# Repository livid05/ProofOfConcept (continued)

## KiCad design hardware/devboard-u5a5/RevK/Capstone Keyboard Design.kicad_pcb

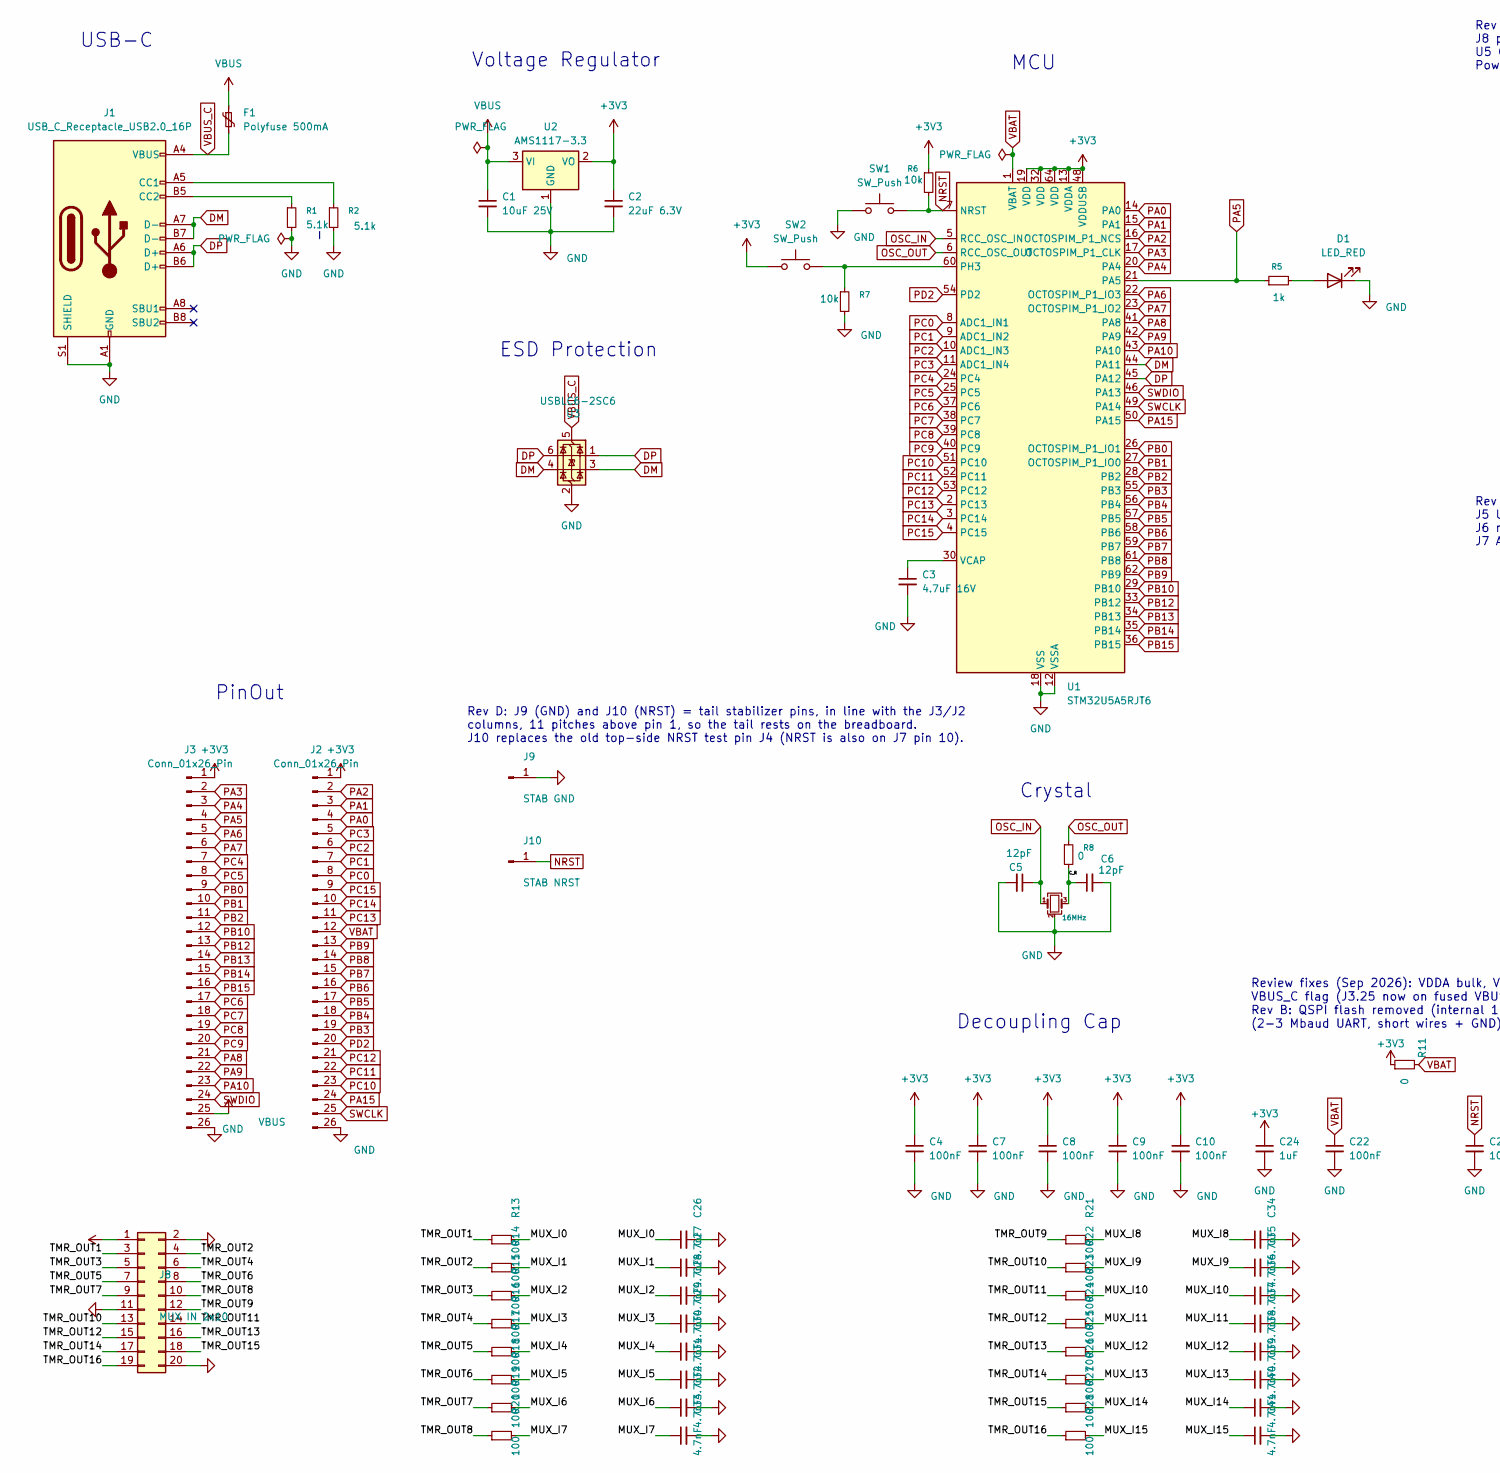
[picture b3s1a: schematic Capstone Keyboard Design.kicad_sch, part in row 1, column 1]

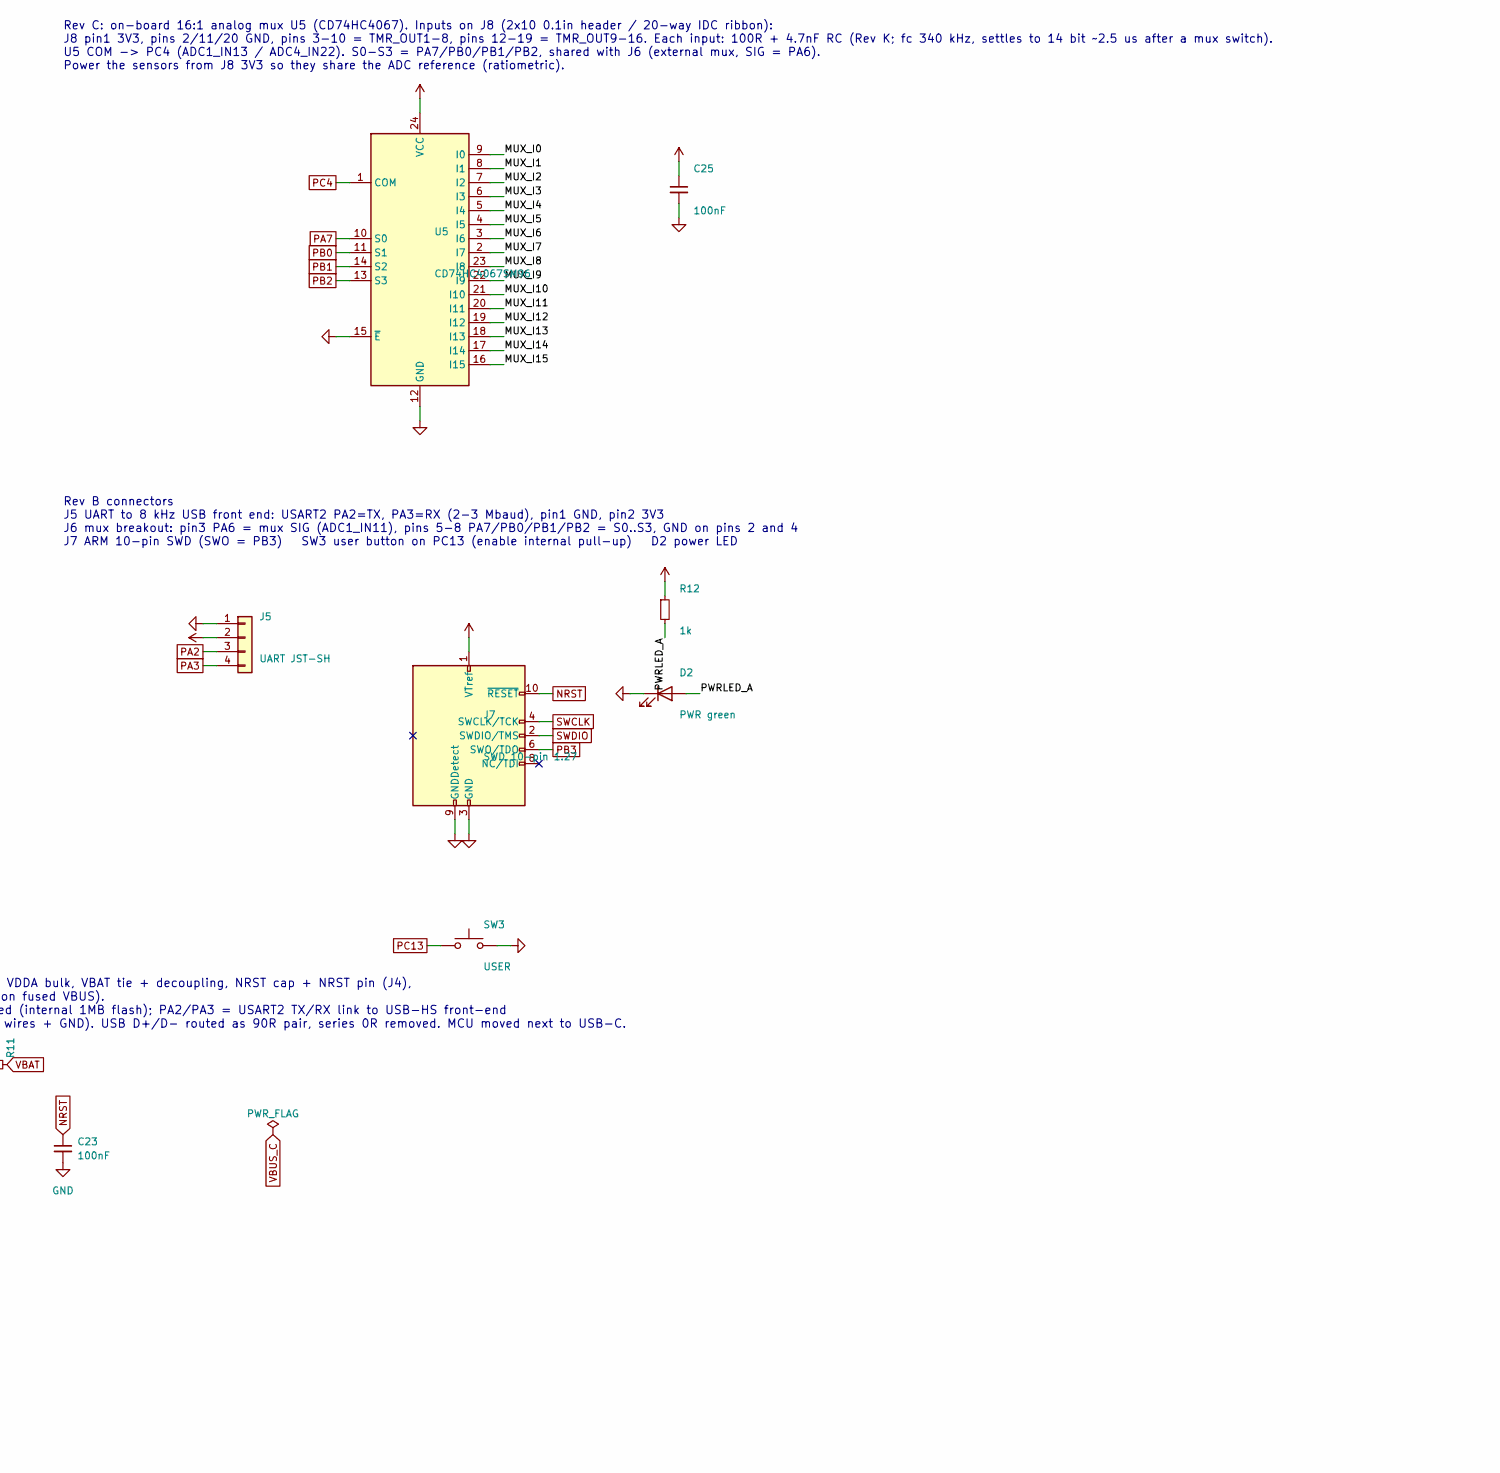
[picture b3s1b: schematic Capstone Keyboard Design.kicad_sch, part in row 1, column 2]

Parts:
C1: 10uF 25V; C_0603_1608Metric_Pad1.08x0.95mm_HandSolder; LCSC C96446
C2: 22uF 6.3V; C_0603_1608Metric_Pad1.08x0.95mm_HandSolder; LCSC C59461
C3: 4.7uF 16V; C_0603_1608Metric_Pad1.08x0.95mm_HandSolder; LCSC C19666
C4, C7, C8, C9, C10, C22, C23: 100nF; C_0402_1005Metric_Pad0.74x0.62mm_HandSolder; LCSC C1525
C5, C6: 12pF; C_0402_1005Metric_Pad0.74x0.62mm_HandSolder; LCSC C1547
C24: 1uF; C_0402_1005Metric_Pad0.74x0.62mm_HandSolder; LCSC C52923
C25: 100nF; C_0402_1005Metric; LCSC C1525
C26, C27, C28, C29, C30, C31, C32, C33, C34, C35, C36, C37, C38, C39, C40, C41: 4.7nF; C_0402_1005Metric; LCSC C1538
D1: LED_RED; LED_0603_1608Metric; LCSC C2286
D2: PWR green; LED_0603_1608Metric; LCSC C12624
F1: Polyfuse 500mA; Fuse_1206_3216Metric_Pad1.42x1.75mm_HandSolder; LCSC C151162
J1: USB_C_Receptacle_USB2.0_16P; USB_C_Receptacle_HRO_TYPE-C-31-M-12; LCSC C165948
J2, J3: Conn_01x26_Pin; PinHeader_1x26_P2.54mm_Vertical
J5: UART JST-SH; JST_SH_SM04B-SRSS-TB_1x04-1MP_P1.00mm_Horizontal; LCSC C160404
J7: SWD 10-pin 1.27; PinHeader_2x05_P1.27mm_Vertical_SMD; LCSC C41376037
J8: MUX IN 2x10; PinHeader_2x10_P2.54mm_Vertical
J9: STAB GND; PinHeader_1x01_P2.54mm_Vertical
J10: STAB NRST; PinHeader_1x01_P2.54mm_Vertical
R1, R2: 5.1k; R_0603_1608Metric_Pad0.98x0.95mm_HandSolder; LCSC C23186
R5: 1k; R_0603_1608Metric_Pad0.98x0.95mm_HandSolder; LCSC C21190
R6, R7: 10k; R_0603_1608Metric_Pad0.98x0.95mm_HandSolder; LCSC C25804
R8, R11: 0; R_0402_1005Metric; LCSC C17168
R12: 1k; R_0603_1608Metric; LCSC C21190
R13, R14, R15, R16, R17, R18, R19, R20, R21, R22, R23, R24, R25, R26, R27, R28: 100; R_0402_1005Metric; LCSC C25076
SW1, SW2: SW_Push; SW_SPST_B3U-1000P; LCSC C231329
SW3: USER; SW_SPST_B3U-1000P; LCSC C231329
U1: STM32U5A5RJT6; LQFP-64_10x10mm_P0.5mm; LCSC C22454506
U2: AMS1117-3.3; SOT-223-3_TabPin2; LCSC C6186
U3: USBLC6-2SC6; SOT-23-6; LCSC C7519
U5: CD74HC4067SM96; SSOP-24_5.3x8.2mm_P0.65mm; LCSC C98457
Y2: 16MHz; Crystal_SMD_3225-4Pin_3.2x2.5mm; LCSC C13738

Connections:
+3V3: C2.1, C4.1, C7.1, C8.1, C9.1, C10.1, C24.1, C25.1, J2.1, J3.1, J5.2, J7.1 (VTref), J8.1, R6.1, R11.1, R12.1, SW2.1, U1.13 (VDDA), U1.19 (VDD), U1.32 (VDD), U1.48 (VDDUSB), U1.64 (VDD), U2.2 (VO), U5.24 (VCC)
/C_R: C6.1, R8.2, Y2.3
/MUX_I0: C26.1, R13.2, U5.9 (I0)
/MUX_I1: C27.1, R14.2, U5.8 (I1)
/MUX_I2: C28.1, R15.2, U5.7 (I2)
/MUX_I3: C29.1, R16.2, U5.6 (I3)
/MUX_I4: C30.1, R17.2, U5.5 (I4)
/MUX_I5: C31.1, R18.2, U5.4 (I5)
/MUX_I6: C32.1, R19.2, U5.3 (I6)
/MUX_I7: C33.1, R20.2, U5.2 (I7)
/MUX_I8: C34.1, R21.2, U5.23 (I8)
/MUX_I9: C35.1, R22.2, U5.22 (I9)
/MUX_I10: C36.1, R23.2, U5.21 (I10)
/MUX_I11: C37.1, R24.2, U5.20 (I11)
/MUX_I12: C38.1, R25.2, U5.19 (I12)
/MUX_I13: C39.1, R26.2, U5.18 (I13)
/MUX_I14: C40.1, R27.2, U5.17 (I14)
/MUX_I15: C41.1, R28.2, U5.16 (I15)
/PWRLED_A: D2.2 (A), R12.2
/TMR_OUT1: J8.3, R13.1
/TMR_OUT2: J8.4, R14.1
/TMR_OUT3: J8.5, R15.1
/TMR_OUT4: J8.6, R16.1
/TMR_OUT5: J8.7, R17.1
/TMR_OUT6: J8.8, R18.1
/TMR_OUT7: J8.9, R19.1
/TMR_OUT8: J8.10, R20.1
/TMR_OUT9: J8.12, R21.1
/TMR_OUT10: J8.13, R22.1
/TMR_OUT11: J8.14, R23.1
/TMR_OUT12: J8.15, R24.1
/TMR_OUT13: J8.16, R25.1
/TMR_OUT14: J8.17, R26.1
/TMR_OUT15: J8.18, R27.1
/TMR_OUT16: J8.19, R28.1
DM: J1.A7 (D-), J1.B7 (D-), U1.44 (PA11), U3.3 (I/O2), U3.4 (I/O2)
DP: J1.A6 (D+), J1.B6 (D+), U1.45 (PA12), U3.1 (I/O1), U3.6 (I/O1)
GND: C1.2, C2.2, C3.2, C4.2, C5.2, C6.2, C7.2, C8.2, C9.2, C10.2, C22.2, C23.2, C24.2, C25.2, C26.2, C27.2, C28.2, C29.2, C30.2, C31.2, C32.2, C33.2, C34.2, C35.2, C36.2, C37.2, C38.2, C39.2, C40.2, C41.2, D1.1 (K), D2.1 (K), J1.A1 (GND), J1.A12 (GND), J1.B1 (GND), J1.B12 (GND), J1.S1 (SHIELD), J2.26, J3.26, J5.1, J7.3 (GND), J7.5 (GND), J7.9 (GNDDetect), J8.2, J8.11, J8.20, J9.1, R1.2, R2.2, R7.2, SW1.1, SW3.2, U1.12 (VSSA), U1.18 (VSS), U1.31 (VSS), U1.47 (VSS), U1.63 (VSS), U2.1 (GND), U3.2 (GND), U5.12 (GND), U5.15 (~E), Y2.2 (G), Y2.4 (G)
NRST: C23.1, J7.10 (~RESET), J10.1, R6.2, SW1.2, U1.7 (NRST)
unnamed: D1.2 (A), R5.2
unnamed: J1.A5 (CC1), R2.1
unnamed: J1.B5 (CC2), R1.1
unnamed: R7.1, SW2.2, U1.60 (PH3)
unnamed: C3.1, U1.30 (VCAP)
OSC_IN: C5.1, U1.5 (RCC_OSC_IN), Y2.1
OSC_OUT: R8.1, U1.6 (RCC_OSC_OUT)
PA0: J2.4, U1.14 (PA0)
PA1: J2.3, U1.15 (PA1)
PA2: J2.2, J5.3, U1.16 (OCTOSPIM_P1_NCS)
PA3: J3.2, J5.4, U1.17 (OCTOSPIM_P1_CLK)
PA4: J3.3, U1.20 (PA4)
PA5: J3.4, R5.1, U1.21 (PA5)
PA6: J3.5, U1.22 (OCTOSPIM_P1_IO3)
PA7: J3.6, U1.23 (OCTOSPIM_P1_IO2), U5.10 (S0)
PA8: J3.21, U1.41 (PA8)
PA9: J3.22, U1.42 (PA9)
PA10: J3.23, U1.43 (PA10)
PA15: J2.24, U1.50 (PA15)
PB0: J3.9, U1.26 (OCTOSPIM_P1_IO1), U5.11 (S1)
PB1: J3.10, U1.27 (OCTOSPIM_P1_IO0), U5.14 (S2)
PB2: J3.11, U1.28 (PB2), U5.13 (S3)
PB3: J2.19, J7.6 (SWO/TDO), U1.55 (PB3)
PB4: J2.18, U1.56 (PB4)
PB5: J2.17, U1.57 (PB5)
PB6: J2.16, U1.58 (PB6)
PB7: J2.15, U1.59 (PB7)
PB8: J2.14, U1.61 (PB8)
PB9: J2.13, U1.62 (PB9)
PB10: J3.12, U1.29 (PB10)
PB12: J3.13, U1.33 (PB12)
PB13: J3.14, U1.34 (PB13)
PB14: J3.15, U1.35 (PB14)
PB15: J3.16, U1.36 (PB15)
PC0: J2.8, U1.8 (ADC1_IN1)
PC1: J2.7, U1.9 (ADC1_IN2)
PC2: J2.6, U1.10 (ADC1_IN3)
PC3: J2.5, U1.11 (ADC1_IN4)
PC4: J3.7, U1.24 (PC4), U5.1 (COM)
PC5: J3.8, U1.25 (PC5)
PC6: J3.17, U1.37 (PC6)
PC7: J3.18, U1.38 (PC7)
PC8: J3.19, U1.39 (PC8)
PC9: J3.20, U1.40 (PC9)
PC10: J2.23, U1.51 (PC10)
PC11: J2.22, U1.52 (PC11)
PC12: J2.21, U1.53 (PC12)
PC13: J2.11, SW3.1, U1.2 (PC13)
PC14: J2.10, U1.3 (PC14)
PC15: J2.9, U1.4 (PC15)
PD2: J2.20, U1.54 (PD2)
SWCLK: J2.25, J7.4 (SWCLK/TCK), U1.49 (PA14)
SWDIO: J3.24, J7.2 (SWDIO/TMS), U1.46 (PA13)
VBAT: C22.1, J2.12, R11.2, U1.1 (VBAT)
VBUS: C1.1, F1.1, J3.25, U2.3 (VI)
VBUS_C: F1.2, J1.A4 (VBUS), J1.A9 (VBUS), J1.B4 (VBUS), J1.B9 (VBUS), U3.5 (VBUS)

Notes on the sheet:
ESD Protection
Voltage Regulator
PinOut
USB-C
Decoupling Cap
Crystal
MCU
Review fixes (Sep 2026): VDDA bulk, VBAT tie + decoupling, NRST cap + NRST pin (J4), VBUS_C flag (J3.25 now on fused VBUS). Rev B: QSPI flash removed (internal 1MB flash); PA2/PA3 = USART2 TX/RX link to USB-HS front-end (2-3 Mbaud UART, short wires + GND). USB D+/D- routed as 90R pair, series 0R re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
Rev B connectors J5 UART to 8 kHz USB front end: USART2 PA2=TX, PA3=RX (2-3 Mbaud), pin1 GND, pin2 3V3 J6 mux breakout: pin3 PA6 = mux SIG (ADC1_IN11), pins 5-8 PA7/PB0/PB1/PB2 = S0..S3, GND on pins 2 and 4 J7 ARM 10-pin SWD (SWO = PB3) SW3 user button on PC13 (enable internal pull-up) D2 power LED
Rev C: on-board 16:1 analog mux U5 (CD74HC4067). Inputs on J8 (2x10 0.1in header / 20-way IDC ribbon): J8 pin1 3V3, pins 2/11/20 GND, pins 3-10 = TMR_OUT1-8, pins 12-19 = TMR_OUT9-16. Each input: 100R + 4.7nF RC (Rev K; fc 340 kHz, settles to 14 bit ~2.5 us after a mux switch). U5 COM -> PC4 (ADC1_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
Rev D: J9 (GND) and J10 (NRST) = tail stabilizer pins, in line with the J3/J2 columns, 11 pitches above pin 1, so the tail rests on the breadboard. J10 replaces the old top-side NRST test pin J4 (NRST is also on J7 pin 10).

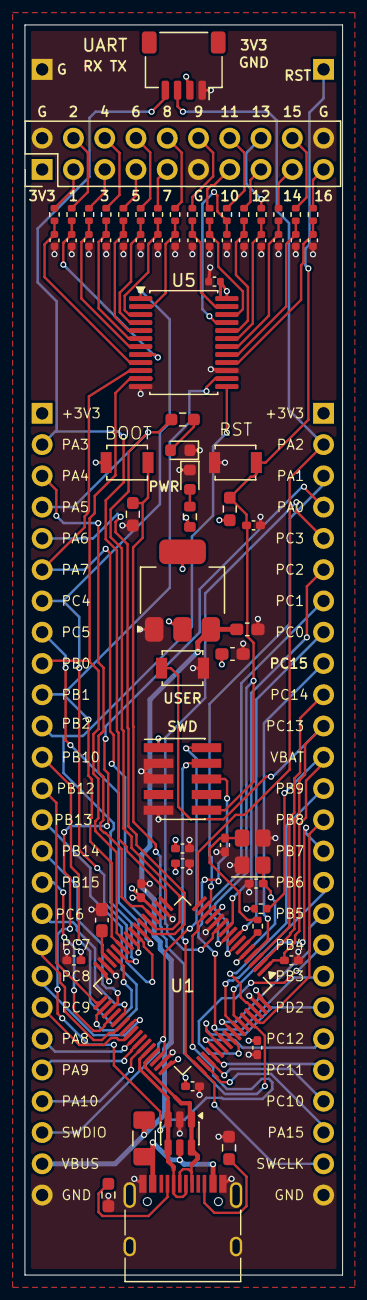
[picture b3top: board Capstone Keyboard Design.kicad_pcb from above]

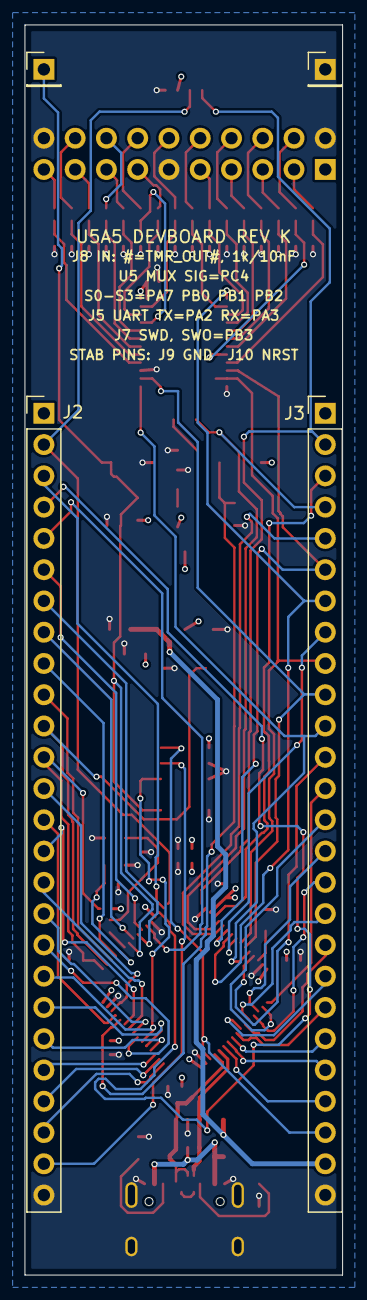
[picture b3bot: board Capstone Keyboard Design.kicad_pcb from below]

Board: 4 copper layers, 25.8 x 101.5 mm, 73 parts (4 on the bottom side), 95 nets.

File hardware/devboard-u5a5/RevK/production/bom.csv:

Comment,Designator,Footprint,LCSC Part #
10uF 25V,C1,0603,C96446
22uF 6.3V,C2,0603,C59461
4.7uF 16V,C3,0603,C19666
100nF,"C4, C7, C8, C9, C10, C22, C23, C25",0402,C1525
12pF,"C5, C6",0402,C1547
1uF,C24,0402,C52923
4.7nF,"C26, C27, C28, C29, C30, C31, C32, C33, C34, C35, C36, C37, C38, C39, C40, C41",0402,C1538
LED_RED,D1,0603,C2286
PWR green,D2,0603,C12624
Polyfuse 500mA,F1,1206,C151162
USB_C_Receptacle_USB2.0_16P,J1,TYPE-C-31-M-12,C165948
UART JST-SH,J5,SM04B-SRSS-TB,C160404
SWD 10-pin 1.27,J7,2x5 1.27mm SMD header,C41376037
5.1k,"R1, R2",0603,C23186
1k,"R5, R12",0603,C21190
10k,"R6, R7",0603,C25804
0,"R8, R11",0402,C17168
100,"R13, R14, R15, R16, R17, R18, R19, R20, R21, R22, R23, R24, R25, R26, R27, R28",0402,C25076
SW_Push,"SW1, SW2",B3U-1000P,C231329
USER,SW3,B3U-1000P,C231329
STM32U5A5RJT6,U1,LQFP-64,C22454506
AMS1117-3.3,U2,SOT-223,C6186
USBLC6-2SC6,U3,SOT-23-6,C7519
CD74HC4067SM96,U5,SSOP-24,C98457
16MHz,Y2,SMD3225-4P,C13738

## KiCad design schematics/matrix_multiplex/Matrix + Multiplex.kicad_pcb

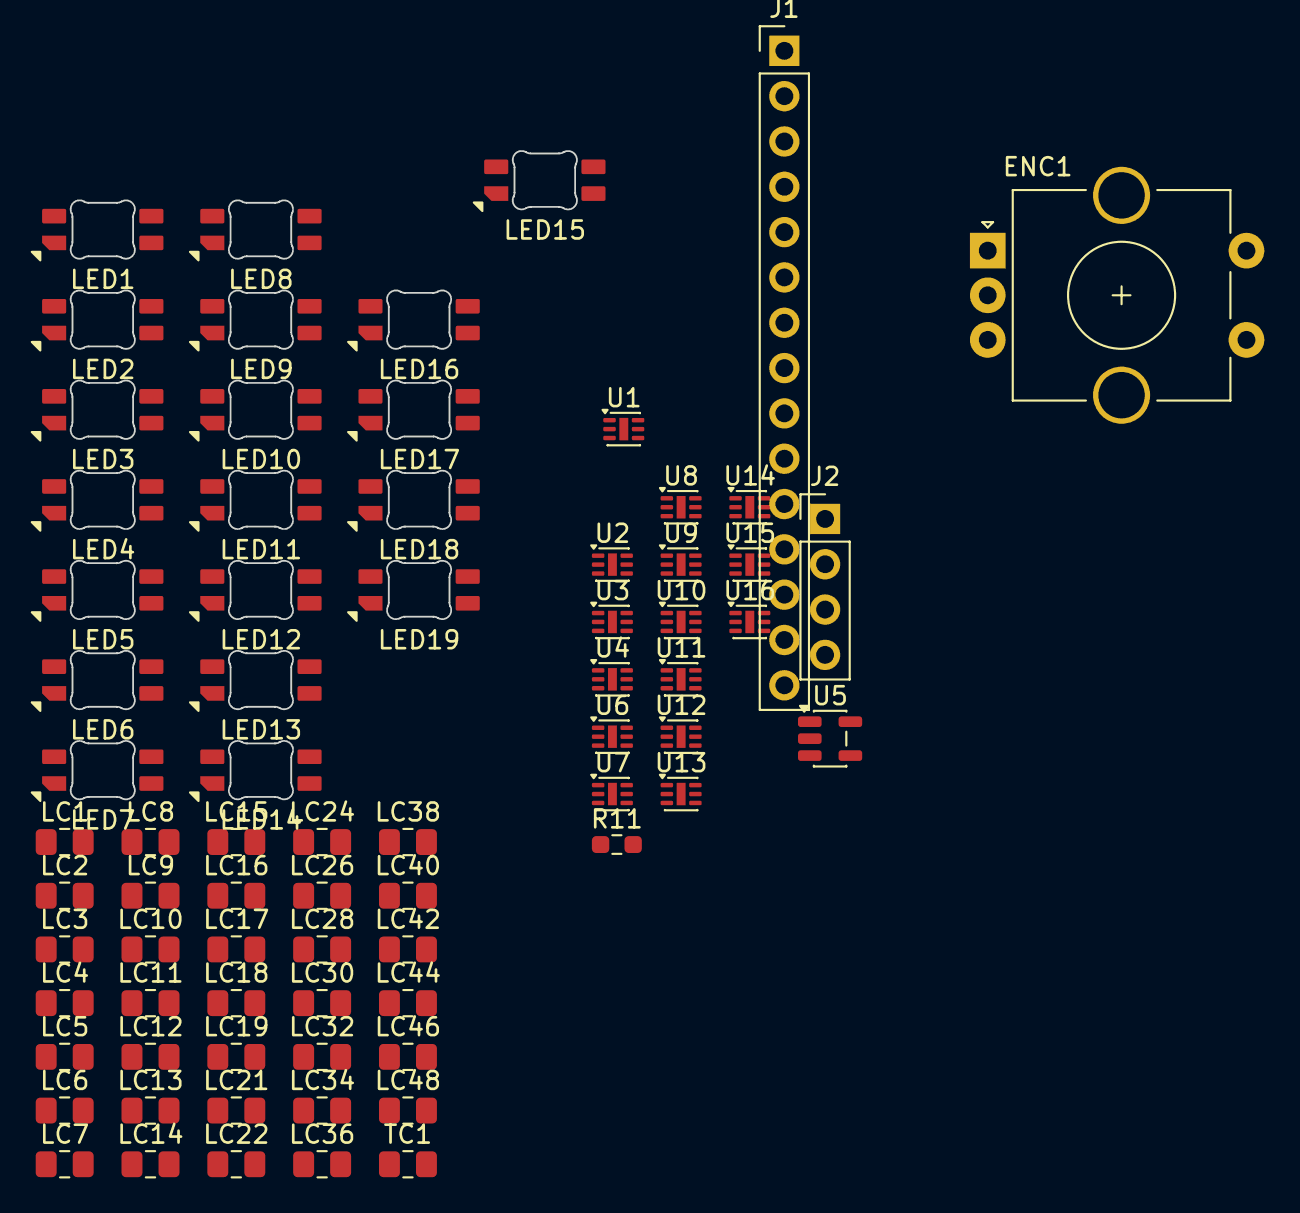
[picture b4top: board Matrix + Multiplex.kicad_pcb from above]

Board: 2 copper layers, 74 parts (0 on the bottom side), 43 nets, no tracks yet.

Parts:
ENC1: RotaryEncoder_Switch_MP; RotaryEncoder_Alps_EC11E-Switch_Vertical_H20mm_CircularMoun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
J1: Conn_01x15_Pin; PinHeader_1x15_P2.54mm_Vertical
J2: Conn_01x04_Pin; PinHeader_1x04_P2.54mm_Vertical
LC1, LC2, LC3, LC4, LC5, LC6, LC7, LC8, LC9, LC10, LC11, LC12, LC13, LC14, LC15, LC16, LC17, LC18, LC19, LC21, LC22, LC24, LC26, LC28, LC30, LC32, LC34, LC36, LC38, LC40, LC42, LC44, LC46, LC48: 0.1uF; C_0805_2012Metric_Pad1.18x1.45mm_HandSolder
LED1, LED2, LED3, LED4, LED5, LED6, LED7, LED8, LED9, LED10, LED11, LED12, LED13, LED14, LED15, LED16, LED17, LED18, LED19: SK6812MINI-E; LED_6028R
R11: 330; R_0603_1608Metric_Pad0.98x0.95mm_HandSolder
TC1: 0.1uF; C_0805_2012Metric_Pad1.18x1.45mm_HandSolder
U1, U2, U3, U4, U6, U7, U8, U9, U10, U11, U12, U13, U14, U15, U16: TMR2615F; MLF-6-1EP_1.6x1.6mm_P0.5mm_EP0.5x1.26mm
U5: SN74LV1T125DBV; SOT-23-5

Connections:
+3.3V: LC21.1, LC22.1, LC26.1, LC28.1, LC30.1, LC32.1, LC34.1, LC36.1, LC38.1, LC40.1, LC42.1, LC44.1, LC46.1, LC48.1, U1.2 (VDD), U2.2 (VDD), U4.2 (VDD), U6.2 (VDD), U7.2 (VDD), U8.2 (VDD), U9.2 (VDD), U10.2 (VDD), U11.2 (VDD), U12.2 (VDD), U13.2 (VDD), U14.2 (VDD), U15.2 (VDD), U16.2 (VDD)
+5V: LC1.1, LC2.1, LC3.1, LC4.1, LC5.1, LC6.1, LC7.1, LC8.1, LC9.1, LC10.1, LC11.1, LC12.1, LC13.1, LC14.1, LC15.1, LC16.1, LC17.1, LC18.1, LC19.1, LED1.1 (VDD), LED2.1 (VDD), LED3.1 (VDD), LED4.1 (VDD), LED5.1 (VDD), LED6.1 (VDD), LED7.1 (VDD), LED8.1 (VDD), LED9.1 (VDD), LED10.1 (VDD), LED11.1 (VDD), LED12.1 (VDD), LED13.1 (VDD), LED14.1 (VDD), LED15.1 (VDD), LED16.1 (VDD), LED17.1 (VDD), LED18.1 (VDD), LED19.1 (VDD), TC1.1, U5.5 (VCC)
ENC_CLK: ENC1.A, J2.1
ENC_DT: ENC1.B, J2.2
ENC_SW: ENC1.S2, J2.3
GND: ENC1.C, ENC1.MP, ENC1.S1, LC1.2, LC2.2, LC3.2, LC4.2, LC5.2, LC6.2, LC7.2, LC8.2, LC9.2, LC10.2, LC11.2, LC12.2, LC13.2, LC14.2, LC15.2, LC16.2, LC17.2, LC18.2, LC19.2, LC21.2, LC22.2, LC24.2, LC26.2, LC28.2, LC30.2, LC32.2, LC34.2, LC36.2, LC38.2, LC40.2, LC42.2, LC44.2, LC46.2, LC48.2, LED1.4 (VSS), LED2.4 (VSS), LED3.4 (VSS), LED4.4 (VSS), LED5.4 (VSS), LED6.4 (VSS), LED7.4 (VSS), LED8.4 (VSS), LED9.4 (VSS), LED10.4 (VSS), LED11.4 (VSS), LED12.4 (VSS), LED13.4 (VSS), LED14.4 (VSS), LED15.4 (VSS), LED16.4 (VSS), LED17.4 (VSS), LED18.4 (VSS), LED19.4 (VSS), TC1.2, U1.3 (GND), U2.3 (GND), U3.3 (GND), U4.3 (GND), U5.1 (~OE), U5.3 (GND), U6.3 (GND), U7.3 (GND), U8.3 (GND), U9.3 (GND), U10.3 (GND), U11.3 (GND), U12.3 (GND), U13.3 (GND), U14.3 (GND), U15.3 (GND), U16.3 (GND)
LED_IN: J2.4, U5.2 (A)
unnamed: LED1.3 (DIN), R11.2
unnamed: LED1.2 (DOUT), LED2.3 (DIN)
unnamed: LED2.2 (DOUT), LED3.3 (DIN)
unnamed: LED3.2 (DOUT), LED4.3 (DIN)
unnamed: LED4.2 (DOUT), LED5.3 (DIN)
unnamed: LED5.2 (DOUT), LED6.3 (DIN)
unnamed: LED6.2 (DOUT), LED7.3 (DIN)
unnamed: LED7.2 (DOUT), LED8.3 (DIN)
unnamed: LED8.2 (DOUT), LED9.3 (DIN)
unnamed: LED9.2 (DOUT), LED10.3 (DIN)
unnamed: LED10.2 (DOUT), LED11.3 (DIN)
unnamed: LED11.2 (DOUT), LED12.3 (DIN)
unnamed: LED12.2 (DOUT), LED13.3 (DIN)
unnamed: LED13.2 (DOUT), LED14.3 (DIN)
unnamed: LED14.2 (DOUT), LED15.3 (DIN)
unnamed: LED15.2 (DOUT), LED16.3 (DIN)
unnamed: LED16.2 (DOUT), LED17.3 (DIN)
unnamed: LED17.2 (DOUT), LED18.3 (DIN)
unnamed: LED18.2 (DOUT), LED19.3 (DIN)
unnamed: LC24.1, U3.2 (VDD)
unnamed: R11.1, U5.4 (Y)
TMR_OUT1: J1.1, U1.1 (VOUT)
TMR_OUT2: J1.2, U2.1 (VOUT)
TMR_OUT3: J1.3, U3.1 (VOUT)
TMR_OUT4: J1.4, U4.1 (VOUT)
TMR_OUT5: J1.5, U6.1 (VOUT)
TMR_OUT6: J1.6, U7.1 (VOUT)
TMR_OUT7: J1.7, U8.1 (VOUT)
TMR_OUT8: J1.8, U9.1 (VOUT)
TMR_OUT9: J1.9, U10.1 (VOUT)
TMR_OUT10: J1.10, U11.1 (VOUT)
TMR_OUT11: J1.11, U12.1 (VOUT)
TMR_OUT12: J1.12, U13.1 (VOUT)
TMR_OUT13: J1.13, U14.1 (VOUT)
TMR_OUT14: J1.14, U15.1 (VOUT)
TMR_OUT15: J1.15, U16.1 (VOUT)

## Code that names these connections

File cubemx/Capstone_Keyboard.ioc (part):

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Mcu.Name=STM32U595RITx
Mcu.Package=LQFP64
Mcu.UserName=STM32U595RITx
RCC.HSE_VALUE=25000000
RCC.HSEState=RCC_HSE_ON
RCC.SYSCLKFreq_VALUE=160000000
RCC.SYSCLKSource=RCC_SYSCLKSOURCE_PLLCLK
PA2.Mode=OCTOSPIM_P1_NCS
PA2.Signal=OCTOSPIM_P1_NCS
PA3.Mode=OCTOSPIM_P1_CLK
PA3.Signal=OCTOSPIM_P1_CLK
PA6.Mode=OCTOSPIM_P1_IO3
PA6.Signal=OCTOSPIM_P1_IO3
PA7.Mode=OCTOSPIM_P1_IO2
PA7.Signal=OCTOSPIM_P1_IO2
PC4.Mode=OCTOSPIM_P1_IO1
PC4.Signal=OCTOSPIM_P1_IO1
PC5.Mode=OCTOSPIM_P1_IO0
PC5.Signal=OCTOSPIM_P1_IO0
PA11.Mode=Device_Only
PA11.Signal=USB_OTG_HS_DM
PA12.Mode=Device_Only
PA12.Signal=USB_OTG_HS_DP
PA13.Mode=Serial_Wire
PA13.Signal=SYS_SWDIO
PA14.Mode=Serial_Wire
PA14.Signal=SYS_SWCLK
PH0-OSC_IN.Mode=HSE-External-Oscillator
PH0-OSC_IN.Signal=RCC_OSC_IN
PH1-OSC_OUT.Mode=HSE-External-Oscillator
PH1-OSC_OUT.Signal=RCC_OSC_OUT
PC0.Mode=IN1-Single-Ended
PC0.Signal=ADC1_INP1
PC1.Mode=IN2-Single-Ended
PC1.Signal=ADC1_INP2
PC2.Mode=IN3-Single-Ended
PC2.Signal=ADC1_INP3
PC3.Mode=IN4-Single-Ended
PC3.Signal=ADC1_INP4
PB6.GPIO_Label=MUX_S0
PB6.GPIO_ModeDefaultEXTI=GPIO_MODE_OUTPUT_PP
PB6.GPIO_PuPd=GPIO_NOPULL
PB6.GPIO_Speed=GPIO_SPEED_FREQ_LOW
PB6.Signal=GPIO_Output
PB7.GPIO_Label=MUX_S1
PB7.GPIO_ModeDefaultEXTI=GPIO_MODE_OUTPUT_PP
PB7.GPIO_PuPd=GPIO_NOPULL
PB7.GPIO_Speed=GPIO_SPEED_FREQ_LOW
PB7.Signal=GPIO_Output
PB8.GPIO_Label=MUX_S2
PB8.GPIO_ModeDefaultEXTI=GPIO_MODE_OUTPUT_PP
PB8.GPIO_PuPd=GPIO_NOPULL
PB8.GPIO_Speed=GPIO_SPEED_FREQ_LOW
PB8.Signal=GPIO_Output
PB9.GPIO_Label=MUX_S3
PB9.GPIO_ModeDefaultEXTI=GPIO_MODE_OUTPUT_PP
PB9.GPIO_PuPd=GPIO_NOPULL
PB9.GPIO_Speed=GPIO_SPEED_FREQ_LOW
PB9.Signal=GPIO_Output
PC6.Mode=Input Capture CH1
PC6.Signal=TIM3_CH1
PC6.GPIO_Label=ENC_CLK
PC7.Mode=Input Capture CH2
PC7.Signal=TIM3_CH2
PC7.GPIO_Label=ENC_DT
PC8.GPIO_Label=ENC_SW
PC8.GPIO_ModeDefaultEXTI=GPIO_MODE_IT_FALLING
PC8.GPIO_PuPd=GPIO_PULLUP
PC8.Signal=GPXTI8
PC9.GPIO_Label=ROW_1
PC9.GPIO_ModeDefaultEXTI=GPIO_MODE_OUTPUT_PP
PC9.GPIO_PuPd=GPIO_NOPULL
PC9.GPIO_Speed=GPIO_SPEED_FREQ_LOW
PC9.Signal=GPIO_Output
PC10.GPIO_Label=ROW_2
PC10.GPIO_ModeDefaultEXTI=GPIO_MODE_OUTPUT_PP
PC10.GPIO_PuPd=GPIO_NOPULL
PC10.GPIO_Speed=GPIO_SPEED_FREQ_LOW
PC10.Signal=GPIO_Output
PC11.GPIO_Label=ROW_3
PC11.GPIO_ModeDefaultEXTI=GPIO_MODE_OUTPUT_PP
PC11.GPIO_PuPd=GPIO_NOPULL
PC11.GPIO_Speed=GPIO_SPEED_FREQ_LOW
PC11.Signal=GPIO_Output
PB5.GPIO_Label=ROW_4
PB5.GPIO_ModeDefaultEXTI=GPIO_MODE_OUTPUT_PP
PB5.GPIO_PuPd=GPIO_NOPULL
PB5.GPIO_Speed=GPIO_SPEED_FREQ_LOW
PB5.Signal=GPIO_Output
PB0.GPIO_Label=COL_1
PB0.GPIO_ModeDefaultEXTI=GPIO_MODE_INPUT
PB0.GPIO_PuPd=GPIO_PULLDOWN
PB0.Signal=GPIO_Input
PB1.GPIO_Label=COL_2
PB1.GPIO_ModeDefaultEXTI=GPIO_MODE_INPUT
PB1.GPIO_PuPd=GPIO_PULLDOWN
PB1.Signal=GPIO_Input
PB2.GPIO_Label=COL_3
PB2.GPIO_ModeDefaultEXTI=GPIO_MODE_INPUT
PB2.GPIO_PuPd=GPIO_PULLDOWN
PB2.Signal=GPIO_Input
PB12.GPIO_Label=COL_4
PB12.GPIO_ModeDefaultEXTI=GPIO_MODE_INPUT
PB12.GPIO_PuPd=GPIO_PULLDOWN
PB12.Signal=GPIO_Input
PB15.Mode=Full_Duplex_Master
PB15.Signal=SPI2_MOSI
PB15.GPIO_Label=LED_DATA
PA9.Mode=Asynchronous
PA9.Signal=USART1_TX
PA10.Mode=Asynchronous
PA10.Signal=USART1_RX
PA0.GPIO_Label=LED_RED
PA0.GPIO_ModeDefaultEXTI=GPIO_MODE_OUTPUT_PP
PA0.GPIO_PuPd=GPIO_NOPULL
PA0.GPIO_Speed=GPIO_SPEED_FREQ_LOW
PA0.Signal=GPIO_Output

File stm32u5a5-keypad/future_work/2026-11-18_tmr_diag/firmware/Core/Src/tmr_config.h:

/* tmr_config.h - every adjustable setting of the TMR sensor test image.
 * DIAGNOSTIC IMAGE ONLY. The keyboard's board_config.h is not used for these
 * and is not changed.
 *
 * Signal path (Devboard RevK + Numpad RevE):
 *   numpad sensor Un pin 1 (TMR_OUTn) -> numpad J1 -> jumper wire ->
 *   devboard J8 hole labelled "n" -> 100 R + 4.7 nF RC -> CD74HC4067 input n-1
 *   -> mux COM -> PC4 = ADC1_IN13 (14-bit).
 * Mux select: S0 = PA7, S1 = PB0, S2 = PB1, S3 = PB2. Mux enable is tied to GND.
 */
#ifndef TMR_CONFIG_H
#define TMR_CONFIG_H

/* ---- Mux and ADC pins (from the RevK netlist) -------------------------- */
#define TMR_MUX_S0_PORT GPIOA
#define TMR_MUX_S0_PIN GPIO_PIN_7
#define TMR_MUX_S1_PORT GPIOB
#define TMR_MUX_S1_PIN GPIO_PIN_0
#define TMR_MUX_S2_PORT GPIOB
#define TMR_MUX_S2_PIN GPIO_PIN_1
#define TMR_MUX_S3_PORT GPIOB
#define TMR_MUX_S3_PIN GPIO_PIN_2
#define TMR_SIG_PORT GPIOC
#define TMR_SIG_PIN GPIO_PIN_4
#define TMR_SIG_PIN_NUMBER 4U       /* bit position of PC4 in MODER/PUPDR */
#define TMR_ADC_CHANNEL ADC_CHANNEL_13

/* User button SW3: PC13 to GND, no external pull-up (internal one used).
 * Pressing it re-runs the self-test, same as typing 't'.
 */
#define TMR_BUTTON_PORT GPIOC
#define TMR_BUTTON_PIN GPIO_PIN_13

/* ---- Channels ------------------------------------------------------------
 * 16 mux inputs. Channel c (0..15) is J8 label c+1 = numpad sensor U(c+1) =
 * key K(c+1). The numpad has 15 sensors; J8 label 16 has nothing on it and
 * should test OPEN, which proves the open-input check works.
 */
#define TMR_CHANNELS 16U
#define TMR_NUMPAD_KEYS 15U

/* Which numpad key (1..15, reading order: top row K1-K4 ... bottom row
 * K13-K15) is wired to J8 hole 1, 2, ... 16. 0 = nothing / unknown.
 * Only used for labels: every usable channel is tested whatever this says.
 *
 * Tyler's bench wiring (2026-11-18, from his description and photos): numpad
 * J1 TMR pins taken in header order (TMR_OUT1, 5, 9, 13, 2, 6, 10, 14, 15,
 * 11, 7, 3, 12, 8, 4) go to J8 holes 16, 14, 12, 10, 7, 5, 3, 1 (the row with
 * 3V3, skipping G and 3V3), then 15, 13, 11, 9, 8, 6, 4. Hole 2 is unused and
 * should test OPEN.
 * If the keys print the wrong K numbers, type 'm' in the console, press
 * K1..K15 in reading order, and paste the line it prints over this one.
 * Plain one-to-one wiring (TMR_OUTn to hole n) would be
 * {1, 2, 3, 4, 5, 6, 7, 8, 9, 10, 11, 12, 13, 14, 15, 0}.
 */
#define TMR_KEY_OF_CHANNEL {14, 0, 10, 4, 6, 8, 2, 12, 3, 13, 7, 9, 11, 5, 15, 1}

/* ---- Timing -------------------------------------------------------------- */
/* Wait after changing the mux address before sampling. RevK's 100 R / 4.7 nF
 * filter plus the mux's 50 pF settle to 14 bits in about 2.5 us; 10 us gives
 * margin for this test. The real keyboard can use less.
 */
#define TMR_MUX_SETTLE_US 10U
/* ADC samples averaged per channel per scan (each about 5-6 us). */
#define TMR_SAMPLES_PER_READ 4U
/* One full 16-channel scan this often (1 kHz is plenty for a test). */
#define TMR_SCAN_PERIOD_US 1000U
/* Open-input probe: how long PC4's internal pull-up/pull-down (~40 k) charges
 * the 4.7 nF filter capacitor before it is read (~16 time constants).
 */
#define TMR_PULL_SETTLE_US 3000U
/* Samples taken per channel for the noise figure in the self-test. */
#define TMR_NOISE_SAMPLES 256U
/* Live line ('l') and LED timing. */
#define TMR_LIVE_PERIOD_MS 250U

/* ---- Press detection (millivolts away from the resting voltage) ----------
 * A key counts as DOWN when its sensor moves this far from rest in EITHER
 * direction (magnet polarity and sensor rotation decide the sign), and UP
 * again when it comes back within TMR_RELEASE_MV. Set the press point to
 * about a third of the swing you see at bottom-out in the 's' summary.
 */
#define TMR_PRESS_MV 150
#define TMR_RELEASE_MV 100
/* A full press should move at least this far for a PASS in the summary. */
#define TMR_GOOD_SWING_MV 300
/* While a key is up and within this window, its rest value follows slow
 * drift (temperature) with a time constant of about TMR_DRIFT_DIV scans.
 */
#define TMR_DRIFT_WINDOW_MV 30
#define TMR_DRIFT_DIV 1024

/* ---- Self-test limits, in per-mille (0.1 %) of the measured VDDA ----------
 * The TMR2615 output rests at half its supply (the part's 500 mV/V offset),
 * so all limits are ratios of the supply instead of fixed millivolts.
 */
#define TMR_OPEN_HIGH_PERMILLE 800    /* pull-up reading above 80 % ...      */
#define TMR_OPEN_LOW_PERMILLE 200     /* ... and pull-down below 20 % = open */
#define TMR_DRIVEN_SPAN_PERMILLE 100  /* pulls move it < 10 %: something drives it */
#define TMR_NOPOWER_LOW_PERMILLE 100  /* pull-down < 10 % and pull-up 10-70 % */
#define TMR_NOPOWER_HIGH_PERMILLE 700 /*   looks like an output with no VDD   */
#define TMR_STUCK_LOW_PERMILLE 50     /* driven but under 5 % of VDDA        */
#define TMR_STUCK_HIGH_PERMILLE 950   /* driven but over 95 % of VDDA        */
#define TMR_REST_MIN_PERMILLE 250     /* healthy rest window: 25 % ...       */
#define TMR_REST_MAX_PERMILLE 750     /* ... to 75 % (nominal 50 %)          */

/* ---- USB IDs ----------------------------------------------------------------
 * ST demonstration VID like the keyboard (0483:5710) and the rate test
 * (0483:5711). Prototype only. tools/tmr-console.ps1 finds the COM port by
 * this pair, so change both together.
 */
#define TMR_USB_VID 0x0483U
#define TMR_USB_PID 0x5712U

#endif
